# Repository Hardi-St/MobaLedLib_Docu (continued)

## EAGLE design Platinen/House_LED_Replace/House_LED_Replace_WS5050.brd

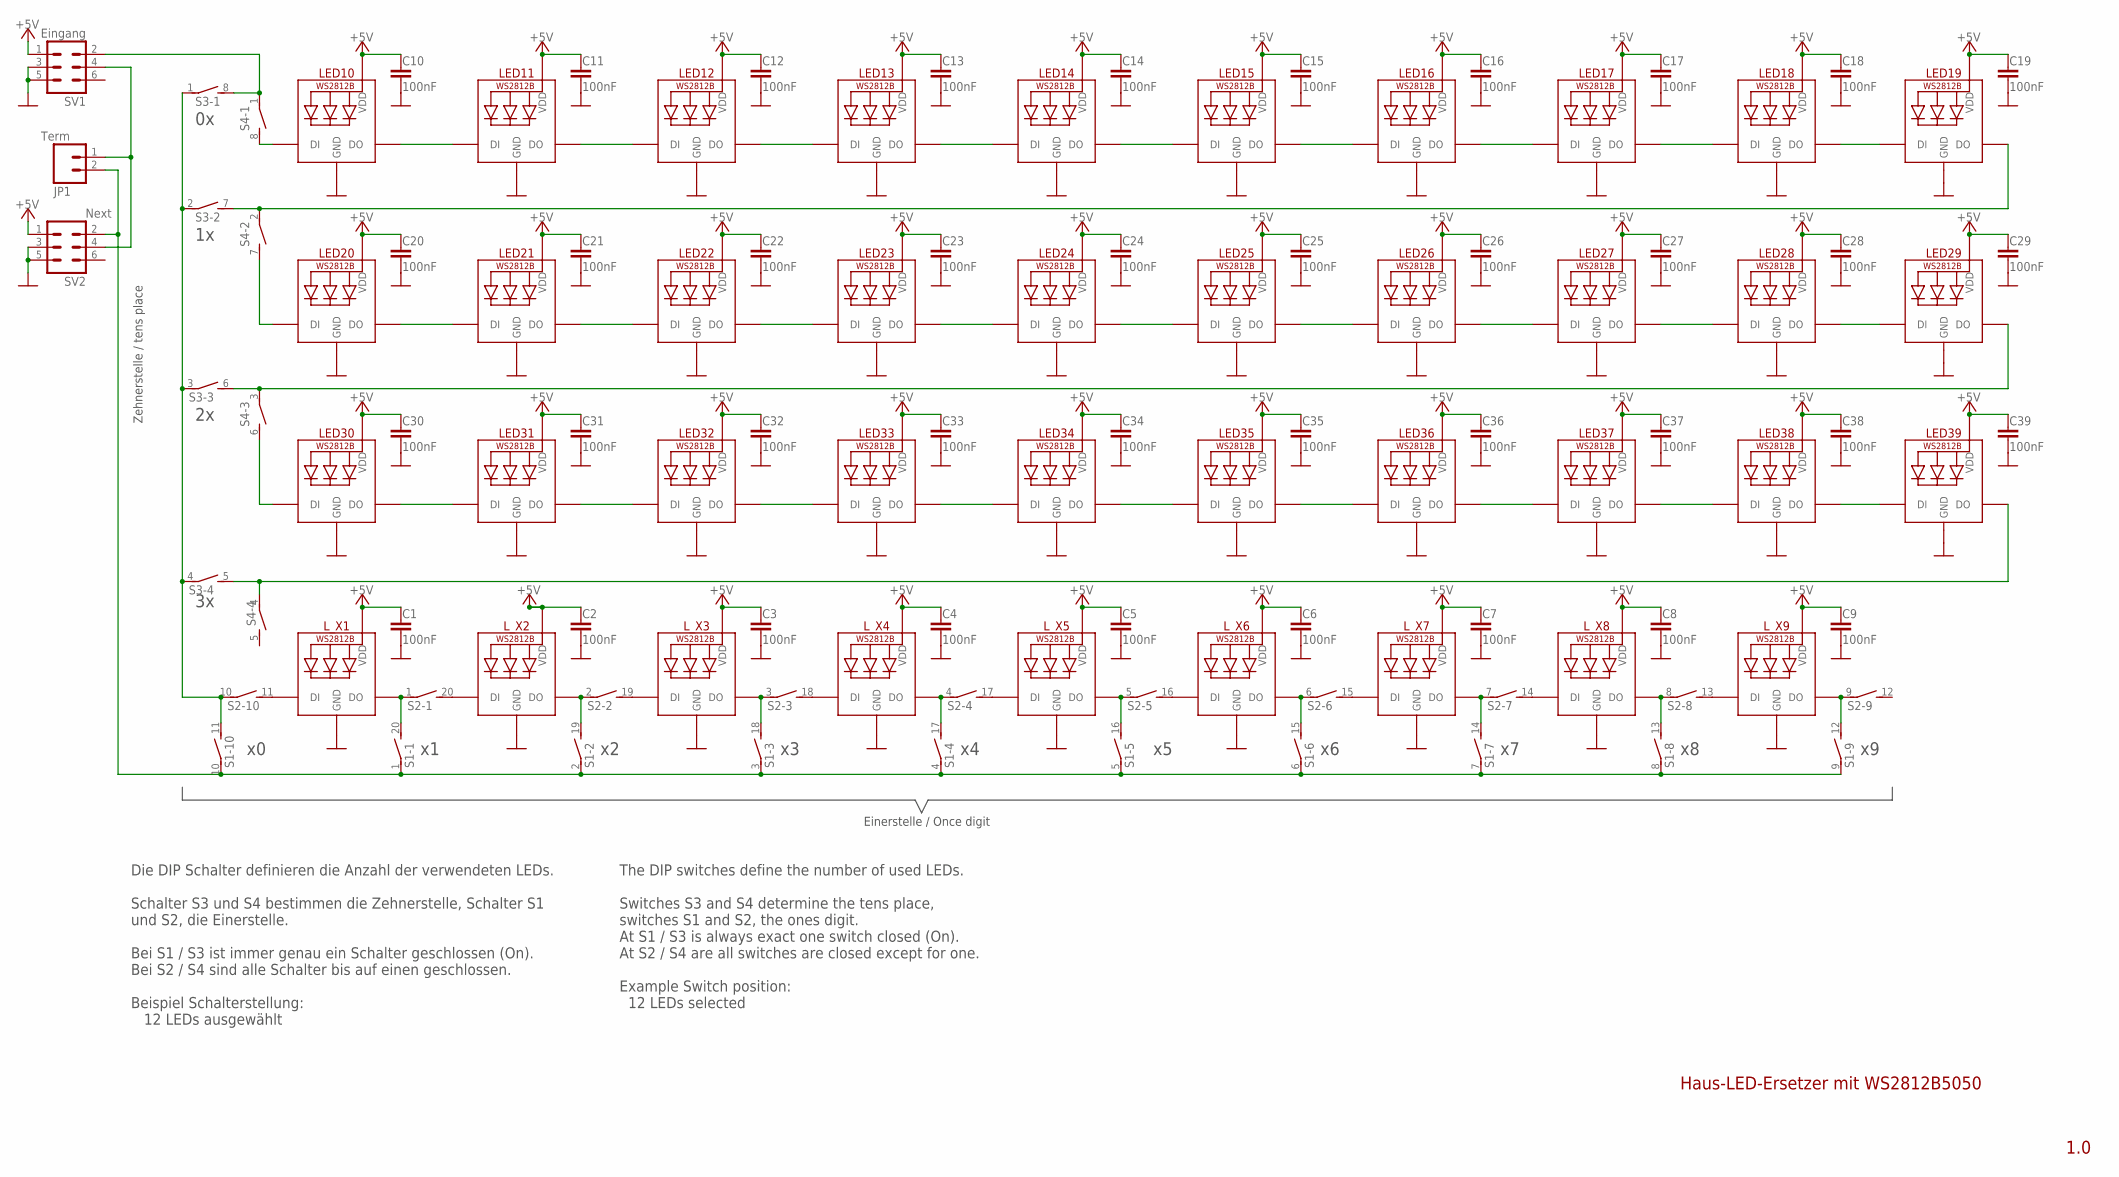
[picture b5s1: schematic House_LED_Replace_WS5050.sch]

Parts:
C1, C2, C3, C4, C5, C6, C7, C8, C9, C10, C11, C12, C13, C14, C15, C16, C17, C18, C19, C20, C21, C22, C23, C24, C25, C26, C27, C28, C29, C30, C31, C32, C33, C34, C35, C36, C37, C38, C39: 100nF; C0603
JP1: Term; 1X02
LED10, LED11, LED12, LED13, LED14, LED15, LED16, LED17, LED18, LED19, LED20, LED21, LED22, LED23, LED24, LED25, LED26, LED27, LED28, LED29, LED30, LED31, LED32, LED33, LED34, LED35, LED36, LED37, LED38, LED39: WS2812B5050; WS2812B
L_X1, L_X2, L_X3, L_X4, L_X5, L_X6, L_X7, L_X8, L_X9: WS2812B5050; WS2812B
S1, S2: DIP10SB
S3, S4: DIP04S
SV1: Eingang; ML6
SV2: Next; ML6

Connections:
+5V: C1.1, C2.1, C3.1, C4.1, C5.1, C6.1, C7.1, C8.1, C9.1, C10.1, C11.1, C12.1, C13.1, C14.1, C15.1, C16.1, C17.1, C18.1, C19.1, C20.1, C21.1, C22.1, C23.1, C24.1, C25.1, C26.1, C27.1, C28.1, C29.1, C30.1, C31.1, C32.1, C33.1, C34.1, C35.1, C36.1, C37.1, C38.1, C39.1, LED10.1-5V (VDD), LED11.1-5V (VDD), LED12.1-5V (VDD), LED13.1-5V (VDD), LED14.1-5V (VDD), LED15.1-5V (VDD), LED16.1-5V (VDD), LED17.1-5V (VDD), LED18.1-5V (VDD), LED19.1-5V (VDD), LED20.1-5V (VDD), LED21.1-5V (VDD), LED22.1-5V (VDD), LED23.1-5V (VDD), LED24.1-5V (VDD), LED25.1-5V (VDD), LED26.1-5V (VDD), LED27.1-5V (VDD), LED28.1-5V (VDD), LED29.1-5V (VDD), LED30.1-5V (VDD), LED31.1-5V (VDD), LED32.1-5V (VDD), LED33.1-5V (VDD), LED34.1-5V (VDD), LED35.1-5V (VDD), LED36.1-5V (VDD), LED37.1-5V (VDD), LED38.1-5V (VDD), LED39.1-5V (VDD), L_X1.1-5V (VDD), L_X2.1-5V (VDD), L_X3.1-5V (VDD), L_X4.1-5V (VDD), L_X5.1-5V (VDD), L_X6.1-5V (VDD), L_X7.1-5V (VDD), L_X8.1-5V (VDD), L_X9.1-5V (VDD), SV1.1, SV2.1
GND: C1.2, C2.2, C3.2, C4.2, C5.2, C6.2, C7.2, C8.2, C9.2, C10.2, C11.2, C12.2, C13.2, C14.2, C15.2, C16.2, C17.2, C18.2, C19.2, C20.2, C21.2, C22.2, C23.2, C24.2, C25.2, C26.2, C27.2, C28.2, C29.2, C30.2, C31.2, C32.2, C33.2, C34.2, C35.2, C36.2, C37.2, C38.2, C39.2, LED10.3-GND (GND), LED11.3-GND (GND), LED12.3-GND (GND), LED13.3-GND (GND), LED14.3-GND (GND), LED15.3-GND (GND), LED16.3-GND (GND), LED17.3-GND (GND), LED18.3-GND (GND), LED19.3-GND (GND), LED20.3-GND (GND), LED21.3-GND (GND), LED22.3-GND (GND), LED23.3-GND (GND), LED24.3-GND (GND), LED25.3-GND (GND), LED26.3-GND (GND), LED27.3-GND (GND), LED28.3-GND (GND), LED29.3-GND (GND), LED30.3-GND (GND), LED31.3-GND (GND), LED32.3-GND (GND), LED33.3-GND (GND), LED34.3-GND (GND), LED35.3-GND (GND), LED36.3-GND (GND), LED37.3-GND (GND), LED38.3-GND (GND), LED39.3-GND (GND), L_X1.3-GND (GND), L_X2.3-GND (GND), L_X3.3-GND (GND), L_X4.3-GND (GND), L_X5.3-GND (GND), L_X6.3-GND (GND), L_X7.3-GND (GND), L_X8.3-GND (GND), L_X9.3-GND (GND), SV1.3, SV1.5, SV2.3, SV2.5
unnamed: JP1.2, S1.1, S1.2 (1), S1.3 (1), S1.4 (1), S1.5 (1), S1.6 (1), S1.7 (1), S1.8 (1), S1.9 (1), S1.10 (1), SV2.2
unnamed: L_X1.2-DOUT (DO), S1.20 (2), S2.1
unnamed: L_X2.4-DIN (DI), S2.20 (2)
unnamed: L_X2.2-DOUT (DO), S1.19 (2), S2.2 (1)
unnamed: L_X3.4-DIN (DI), S2.19 (2)
unnamed: L_X3.2-DOUT (DO), S1.18 (2), S2.3 (1)
unnamed: L_X4.4-DIN (DI), S2.18 (2)
unnamed: L_X4.2-DOUT (DO), S1.17 (2), S2.4 (1)
unnamed: LED10.2-DOUT (DO), LED11.4-DIN (DI)
unnamed: LED11.2-DOUT (DO), LED12.4-DIN (DI)
unnamed: LED12.2-DOUT (DO), LED13.4-DIN (DI)
unnamed: LED13.2-DOUT (DO), LED14.4-DIN (DI)
unnamed: LED14.2-DOUT (DO), LED15.4-DIN (DI)
unnamed: LED15.2-DOUT (DO), LED16.4-DIN (DI)
unnamed: LED16.2-DOUT (DO), LED17.4-DIN (DI)
unnamed: LED17.2-DOUT (DO), LED18.4-DIN (DI)
unnamed: LED18.2-DOUT (DO), LED19.4-DIN (DI)
unnamed: LED30.2-DOUT (DO), LED31.4-DIN (DI)
unnamed: LED20.2-DOUT (DO), LED21.4-DIN (DI)
unnamed: LED21.2-DOUT (DO), LED22.4-DIN (DI)
unnamed: LED22.2-DOUT (DO), LED23.4-DIN (DI)
unnamed: LED23.2-DOUT (DO), LED24.4-DIN (DI)
unnamed: LED24.2-DOUT (DO), LED25.4-DIN (DI)
unnamed: LED25.2-DOUT (DO), LED26.4-DIN (DI)
unnamed: LED26.2-DOUT (DO), LED27.4-DIN (DI)
unnamed: LED27.2-DOUT (DO), LED28.4-DIN (DI)
unnamed: LED28.2-DOUT (DO), LED29.4-DIN (DI)
unnamed: LED31.2-DOUT (DO), LED32.4-DIN (DI)
unnamed: LED32.2-DOUT (DO), LED33.4-DIN (DI)
unnamed: LED33.2-DOUT (DO), LED34.4-DIN (DI)
unnamed: LED34.2-DOUT (DO), LED35.4-DIN (DI)
unnamed: LED35.2-DOUT (DO), LED36.4-DIN (DI)
unnamed: LED36.2-DOUT (DO), LED37.4-DIN (DI)
unnamed: LED37.2-DOUT (DO), LED38.4-DIN (DI)
unnamed: LED38.2-DOUT (DO), LED39.4-DIN (DI)
unnamed: L_X5.4-DIN (DI), S2.17 (2)
unnamed: L_X5.2-DOUT (DO), S1.16 (2), S2.5 (1)
unnamed: LED19.2-DOUT (DO), S3.7 (2), S4.2 (1)
unnamed: LED20.4-DIN (DI), S4.7 (2)
unnamed: L_X6.4-DIN (DI), S2.16 (2)
unnamed: LED30.4-DIN (DI), S4.6 (2)
unnamed: LED39.2-DOUT (DO), S3.5 (2), S4.4 (1)
unnamed: L_X6.2-DOUT (DO), S1.15 (2), S2.6 (1)
unnamed: L_X7.4-DIN (DI), S2.15 (2)
unnamed: L_X7.2-DOUT (DO), S1.14 (2), S2.7 (1)
unnamed: L_X8.4-DIN (DI), S2.14 (2)
unnamed: L_X8.2-DOUT (DO), S1.13 (2), S2.8 (1)
unnamed: LED10.4-DIN (DI), S4.8 (2)
unnamed: S3.8 (2), S4.1, SV1.2
unnamed: S1.11 (2), S2.10 (1), S3.1, S3.2 (1), S3.3 (1), S3.4 (1)
unnamed: L_X9.4-DIN (DI), S2.13 (2)
unnamed: L_X9.2-DOUT (DO), S1.12 (2), S2.9 (1)
unnamed: L_X1.4-DIN (DI), S2.11 (2)
unnamed: JP1.1, SV1.4, SV2.4
unnamed: LED29.2-DOUT (DO), S3.6 (2), S4.3 (1)

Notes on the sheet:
Die DIP Schalter definieren die Anzahl der verwendeten LEDs. Schalter S3 und S4 bestimmen die Zehnerstelle, Schalter S1 und S2, die Einerstelle. Bei S1 / S3 ist immer genau ein Schalter geschlossen (On). Bei S2 / S4 sind alle Schalter bis auf einen geschlossen. Beispiel Schalterstellung: 12 LEDs au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
Zehnerstelle / tens place
Einerstelle / Once digit
1.0
Haus-LED-Ersetzer mit WS2812B5050
The DIP switches define the number of used LEDs. Switches S3 and S4 determine the tens place, switches S1 and S2, the ones digit. At S1 / S3 is always exact one switch closed (On). At S2 / S4 are all switches are closed except for one. Example Switch position: 12 LEDs selected

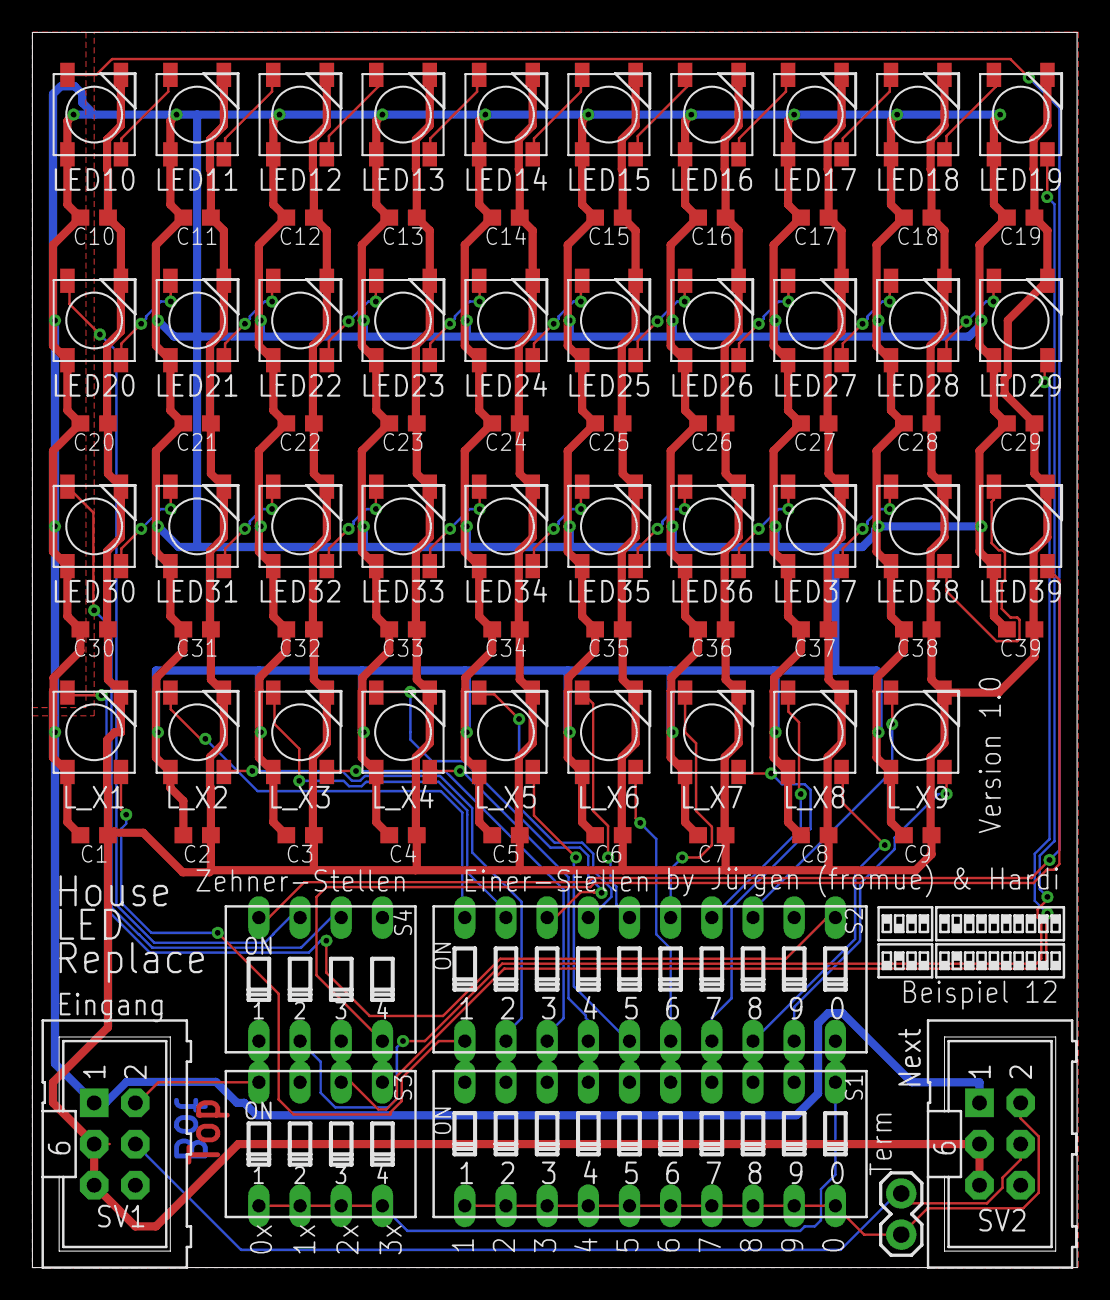
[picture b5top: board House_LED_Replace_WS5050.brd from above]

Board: 2 copper layers, 64.4 x 76.2 mm, 85 parts (0 on the bottom side), 57 nets.

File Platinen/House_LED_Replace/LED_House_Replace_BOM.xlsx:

Comment | Designator | Footprint | JLCPCB Part #（optional）
100nF | C1, C2, C3, C4, C5, C6, C7, C8, C9, C10, C11, C12, C13, C14, C15, C16, C17, C18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 | C0603 | C14663
WS2812B5050 | L_X1, L_X2, L_X3, L_X4, L_X5, L_X6, L_X7, L_X8, L_X9, LED10, LED11, LED12, LED1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 | WS2812B5050 | C2761795

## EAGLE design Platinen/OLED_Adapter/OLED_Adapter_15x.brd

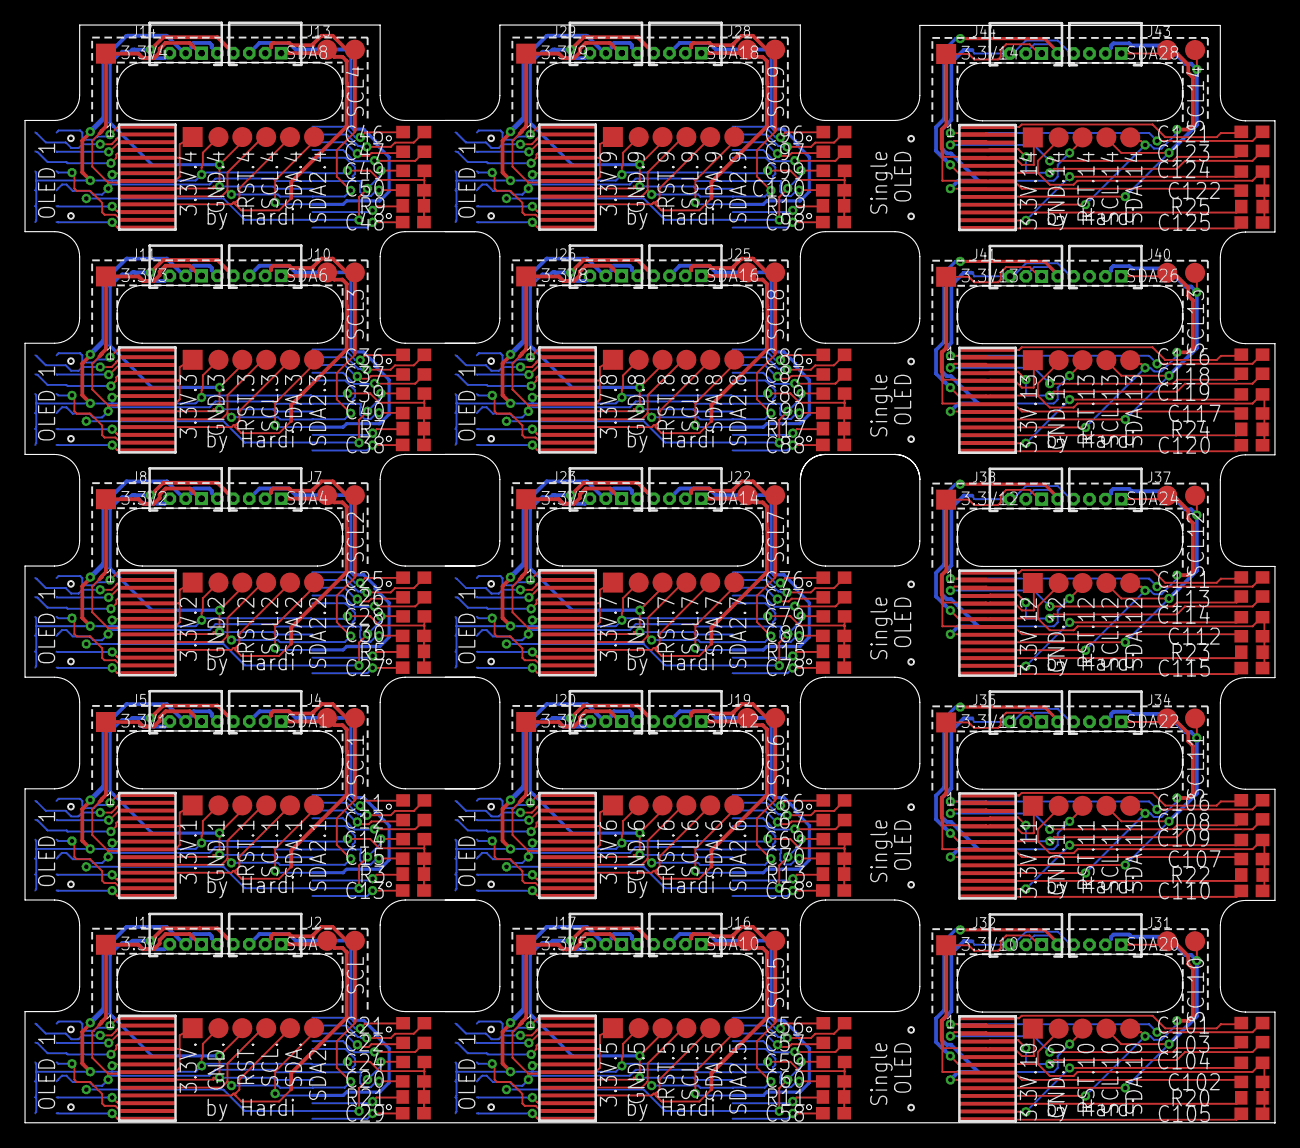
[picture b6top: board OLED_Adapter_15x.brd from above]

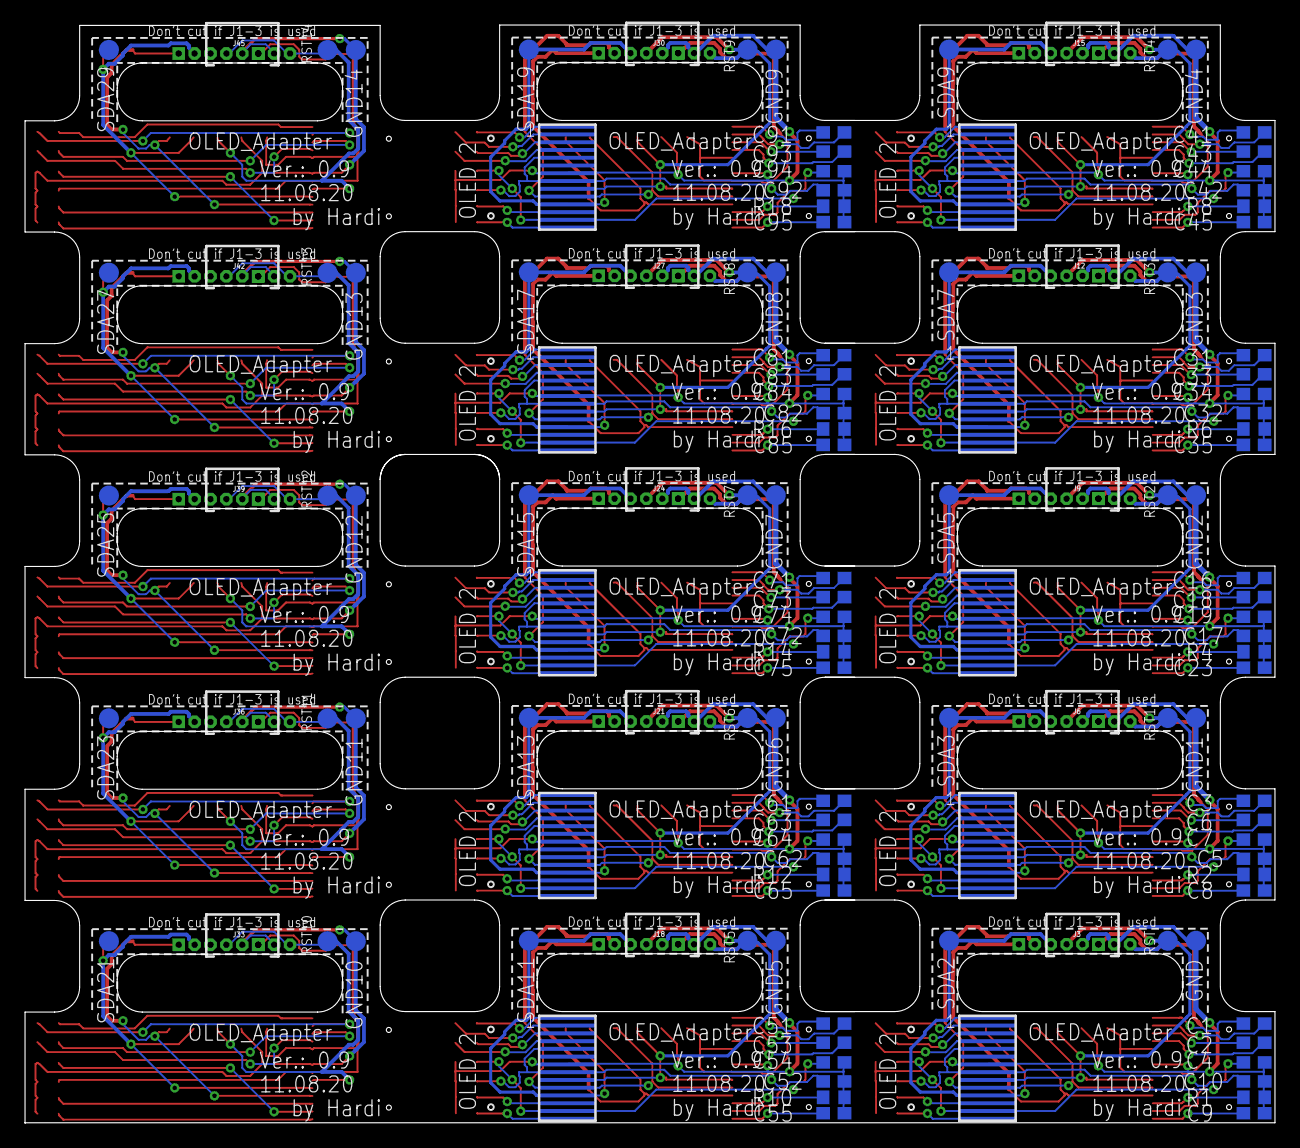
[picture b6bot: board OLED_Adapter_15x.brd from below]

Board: 2 copper layers, 99.8 x 87.7 mm, 395 parts (130 on the bottom side), 260 nets.

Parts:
3.3V, 3.3V1, 3.3V2, 3.3V3, 3.3V4, 3.3V5, 3.3V6, 3.3V7, 3.3V8, 3.3V9, 3.3V10, 3.3V11, 3.3V12, 3.3V13, 3.3V14: 3.3V; TP16SQ
3.3V., 3.3V.1, 3.3V.2, 3.3V.3, 3.3V.4, 3.3V.5, 3.3V.6, 3.3V.7, 3.3V.8, 3.3V.9, 3.3V.10, 3.3V.11, 3.3V.12, 3.3V.13, 3.3V.14: TPTP16SQ; TP16SQ
C1, C2, C3, C6, C11, C12, C16, C18, C21, C22, C25, C26, C31, C33, C36, C37, C41, C43, C46, C47, C51, C53, C56, C57, C61, C63, C66, C67, C71, C73, C76, C77, C81, C83, C86, C87, C91, C93, C96, C97, C101, C103, C106, C108, C111, C113, C116, C118, C121, C123: 470nF; C0603
C4, C7, C14, C19, C24, C28, C34, C39, C44, C49, C54, C59, C64, C69, C74, C79, C84, C89, C94, C99, C104, C109, C114, C119, C124: 2.2uF; C0603
C5, C8, C9, C10, C13, C15, C17, C20, C23, C27, C29, C30, C32, C35, C38, C40, C42, C45, C48, C50, C52, C55, C58, C60, C62, C65, C68, C70, C72, C75, C78, C80, C82, C85, C88, C90, C92, C95, C98, C100, C102, C105, C107, C110, C112, C115, C117, C120, C122, C125: 4.7uF; C0603
GND, GND1, GND2, GND3, GND4, GND5, GND6, GND7, GND8, GND9, GND10, GND11, GND12, GND13, GND14: GND; TP16R
GND., GND.1, GND.2, GND.3, GND.4, GND.5, GND.6, GND.7, GND.8, GND.9, GND.10, GND.11, GND.12, GND.13, GND.14: TPTP16R; TP16R
IC1, IC2, IC3, IC4, IC5, IC6, IC7, IC8, IC9, IC10, IC11, IC12, IC13, IC14, IC15, IC16, IC17, IC18, IC19, IC20, IC21, IC22, IC23, IC24, IC25: OLED_FLEXW_DISP; OLED_FLEX_W_DISP
J1, J2, J3, J4, J5, J6, J7, J8, J9, J10, J11, J12, J13, J14, J15, J16, J17, J18, J19, J20, J21, J22, J23, J24, J25, J26, J27, J28, J29, J30, J31, J32, J33, J34, J35, J36, J37, J38, J39, J40, J41, J42, J43, J44, J45: SV3; MINI
R1, R2, R3, R4, R5, R6, R7, R8, R9, R10, R11, R12, R13, R14, R15, R16, R17, R18, R19, R20, R21, R22, R23, R24, R25: 560K; R0603
RST, RST1, RST2, RST3, RST4, RST5, RST6, RST7, RST8, RST9, RST10, RST11, RST12, RST13, RST14: RST; TP16R
RST., RST.1, RST.2, RST.3, RST.4, RST.5, RST.6, RST.7, RST.8, RST.9, RST.10, RST.11, RST.12, RST.13, RST.14: TPTP16R; TP16R
SCL, SCL1, SCL2, SCL3, SCL4, SCL5, SCL6, SCL7, SCL8, SCL9, SCL10, SCL11, SCL12, SCL13, SCL14: SCL; TP16R
SCL., SCL.1, SCL.2, SCL.3, SCL.4, SCL.5, SCL.6, SCL.7, SCL.8, SCL.9, SCL.10, SCL.11, SCL.12, SCL.13, SCL.14: TPTP16R; TP16R
SDA, SDA1, SDA4, SDA6, SDA8, SDA10, SDA12, SDA14, SDA16, SDA18, SDA20, SDA22, SDA24, SDA26, SDA28: SDA; TP16R
SDA2, SDA3, SDA5, SDA7, SDA9, SDA11, SDA13, SDA15, SDA17, SDA19, SDA21, SDA23, SDA25, SDA27, SDA29: SDA2; TP16R
SDA2., SDA2.1, SDA2.2, SDA2.3, SDA2.4, SDA2.5, SDA2.6, SDA2.7, SDA2.8, SDA2.9, SDA., SDA.1, SDA.2, SDA.3, SDA.4, SDA.5, SDA.6, SDA.7, SDA.8, SDA.9, SDA.10, SDA.11, SDA.12, SDA.13, SDA.14: TPTP16R; TP16R

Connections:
3.3V: 3.3V.TP, 3.3V..TP, C10.1, C20.1, IC1.5, IC1.8, IC2.5, IC2.8, J1.1, J3.1
3.3V1: 3.3V1.TP, 3.3V.1.TP, C5.1, C15.1, IC3.5, IC3.8, IC4.5, IC4.8, J5.1, J6.1
3.3V2: 3.3V2.TP, 3.3V.2.TP, C17.1, C30.1, IC5.5, IC5.8, IC6.5, IC6.8, J8.1, J9.1
3.3V3: 3.3V3.TP, 3.3V.3.TP, C32.1, C40.1, IC7.5, IC7.8, IC8.5, IC8.8, J11.1, J12.1
3.3V4: 3.3V4.TP, 3.3V.4.TP, C42.1, C50.1, IC9.5, IC9.8, IC10.5, IC10.8, J14.1, J15.1
3.3V5: 3.3V5.TP, 3.3V.5.TP, C52.1, C60.1, IC11.5, IC11.8, IC12.5, IC12.8, J17.1, J18.1
3.3V6: 3.3V6.TP, 3.3V.6.TP, C62.1, C70.1, IC13.5, IC13.8, IC14.5, IC14.8, J20.1, J21.1
3.3V7: 3.3V7.TP, 3.3V.7.TP, C72.1, C80.1, IC15.5, IC15.8, IC16.5, IC16.8, J23.1, J24.1
3.3V8: 3.3V8.TP, 3.3V.8.TP, C82.1, C90.1, IC17.5, IC17.8, IC18.5, IC18.8, J26.1, J27.1
3.3V9: 3.3V9.TP, 3.3V.9.TP, C92.1, C100.1, IC19.5, IC19.8, IC20.5, IC20.8, J29.1, J30.1
3.3V10: 3.3V10.TP, 3.3V.10.TP, C102.1, IC21.5, IC21.8, J32.1, J33.1
3.3V11: 3.3V11.TP, 3.3V.11.TP, C107.1, IC22.5, IC22.8, J35.1, J36.1
3.3V12: 3.3V12.TP, 3.3V.12.TP, C112.1, IC23.5, IC23.8, J38.1, J39.1
3.3V13: 3.3V13.TP, 3.3V.13.TP, C117.1, IC24.5, IC24.8, J41.1, J42.1
3.3V14: 3.3V14.TP, 3.3V.14.TP, C122.1, IC25.5, IC25.8, J44.1, J45.1
GND: C4.1, C9.2, C10.2, C20.2, C24.1, C29.2, GND.TP, GND..TP, IC1.7, IC2.7, J1.2, J3.2, R1.1, R21.1
GND1: C5.2, C7.1, C8.2, C13.2, C14.1, C15.2, GND1.TP, GND.1.TP, IC3.7, IC4.7, J5.2, J6.2, R2.1, R3.1
GND2: C17.2, C19.1, C23.2, C27.2, C28.1, C30.2, GND2.TP, GND.2.TP, IC5.7, IC6.7, J8.2, J9.2, R4.1, R5.1
GND3: C32.2, C34.1, C35.2, C38.2, C39.1, C40.2, GND3.TP, GND.3.TP, IC7.7, IC8.7, J11.2, J12.2, R6.1, R7.1
GND4: C42.2, C44.1, C45.2, C48.2, C49.1, C50.2, GND4.TP, GND.4.TP, IC9.7, IC10.7, J14.2, J15.2, R8.1, R9.1
GND5: C52.2, C54.1, C55.2, C58.2, C59.1, C60.2, GND5.TP, GND.5.TP, IC11.7, IC12.7, J17.2, J18.2, R10.1, R11.1
GND6: C62.2, C64.1, C65.2, C68.2, C69.1, C70.2, GND6.TP, GND.6.TP, IC13.7, IC14.7, J20.2, J21.2, R12.1, R13.1
GND7: C72.2, C74.1, C75.2, C78.2, C79.1, C80.2, GND7.TP, GND.7.TP, IC15.7, IC16.7, J23.2, J24.2, R14.1, R15.1
GND8: C82.2, C84.1, C85.2, C88.2, C89.1, C90.2, GND8.TP, GND.8.TP, IC17.7, IC18.7, J26.2, J27.2, R16.1, R17.1
GND9: C92.2, C94.1, C95.2, C98.2, C99.1, C100.2, GND9.TP, GND.9.TP, IC19.7, IC20.7, J29.2, J30.2, R18.1, R19.1
GND10: C102.2, C104.1, C105.2, GND10.TP, GND.10.TP, IC21.7, J32.2, J33.2, R20.1
GND11: C107.2, C109.1, C110.2, GND11.TP, GND.11.TP, IC22.7, J35.2, J36.2, R22.1
GND12: C112.2, C114.1, C115.2, GND12.TP, GND.12.TP, IC23.7, J38.2, J39.2, R23.1
GND13: C117.2, C119.1, C120.2, GND13.TP, GND.13.TP, IC24.7, J41.2, J42.2, R24.1
GND14: C122.2, C124.1, C125.2, GND14.TP, GND.14.TP, IC25.7, J44.2, J45.2, R25.1
unnamed: IC1.12, R1.2
unnamed: C21.2, IC2.1
unnamed: C1.2, IC1.1
unnamed: C1.1, IC1.2
unnamed: C2.2, IC1.3
unnamed: C2.1, IC1.4
unnamed: C9.1, IC1.14
unnamed: C4.2, IC1.13
unnamed: C21.1, IC2.2
unnamed: C22.2, IC2.3
unnamed: C22.1, IC2.4
unnamed: IC2.12, R21.2
unnamed: C29.1, IC2.14
unnamed: C24.2, IC2.13
unnamed: C3.2, IC3.1
unnamed: C3.1, IC3.2
unnamed: C6.2, IC3.3
unnamed: C6.1, IC3.4
unnamed: IC3.12, R2.2
unnamed: C8.1, IC3.14
unnamed: C7.2, IC3.13
unnamed: C11.2, IC4.1
unnamed: C11.1, IC4.2
unnamed: C12.2, IC4.3
unnamed: C12.1, IC4.4
unnamed: IC4.12, R3.2
unnamed: C13.1, IC4.14
unnamed: C14.2, IC4.13
unnamed: C16.2, IC5.1
unnamed: C16.1, IC5.2
unnamed: C18.2, IC5.3
unnamed: C18.1, IC5.4
unnamed: IC5.12, R4.2
unnamed: C23.1, IC5.14
unnamed: C19.2, IC5.13
unnamed: C25.2, IC6.1
unnamed: C25.1, IC6.2
unnamed: C26.2, IC6.3
unnamed: C26.1, IC6.4
unnamed: IC6.12, R5.2
unnamed: C27.1, IC6.14
unnamed: C28.2, IC6.13
unnamed: C31.2, IC7.1
unnamed: C31.1, IC7.2
unnamed: C33.2, IC7.3
unnamed: C33.1, IC7.4
unnamed: IC7.12, R6.2
unnamed: C35.1, IC7.14
unnamed: C34.2, IC7.13
unnamed: C36.2, IC8.1
unnamed: C36.1, IC8.2
unnamed: C37.2, IC8.3
unnamed: C37.1, IC8.4
unnamed: IC8.12, R7.2
unnamed: C38.1, IC8.14
unnamed: C39.2, IC8.13
unnamed: C41.2, IC9.1
unnamed: C41.1, IC9.2
unnamed: C43.2, IC9.3
unnamed: C43.1, IC9.4
unnamed: IC9.12, R8.2
unnamed: C45.1, IC9.14
unnamed: C44.2, IC9.13
unnamed: C46.2, IC10.1
unnamed: C46.1, IC10.2
unnamed: C47.2, IC10.3
unnamed: C47.1, IC10.4
unnamed: IC10.12, R9.2
unnamed: C48.1, IC10.14
unnamed: C49.2, IC10.13
unnamed: C51.2, IC11.1
unnamed: C51.1, IC11.2
unnamed: C53.2, IC11.3
unnamed: C53.1, IC11.4
unnamed: IC11.12, R10.2
unnamed: C55.1, IC11.14
unnamed: C54.2, IC11.13
unnamed: C56.2, IC12.1
unnamed: C56.1, IC12.2
unnamed: C57.2, IC12.3
unnamed: C57.1, IC12.4
unnamed: IC12.12, R11.2
unnamed: C58.1, IC12.14
unnamed: C59.2, IC12.13
unnamed: C61.2, IC13.1
unnamed: C61.1, IC13.2
unnamed: C63.2, IC13.3
unnamed: C63.1, IC13.4
unnamed: IC13.12, R12.2
unnamed: C65.1, IC13.14
unnamed: C64.2, IC13.13
unnamed: C66.2, IC14.1
unnamed: C66.1, IC14.2
unnamed: C67.2, IC14.3
unnamed: C67.1, IC14.4
unnamed: IC14.12, R13.2
unnamed: C68.1, IC14.14
unnamed: C69.2, IC14.13
unnamed: C71.2, IC15.1
unnamed: C71.1, IC15.2
unnamed: C73.2, IC15.3
unnamed: C73.1, IC15.4
unnamed: IC15.12, R14.2
unnamed: C75.1, IC15.14
unnamed: C74.2, IC15.13
unnamed: C76.2, IC16.1
unnamed: C76.1, IC16.2
unnamed: C77.2, IC16.3
unnamed: C77.1, IC16.4
unnamed: IC16.12, R15.2
unnamed: C78.1, IC16.14
unnamed: C79.2, IC16.13
unnamed: C81.2, IC17.1
unnamed: C81.1, IC17.2
unnamed: C83.2, IC17.3
unnamed: C83.1, IC17.4
unnamed: IC17.12, R16.2
unnamed: C85.1, IC17.14
unnamed: C84.2, IC17.13
unnamed: C86.2, IC18.1
unnamed: C86.1, IC18.2
unnamed: C87.2, IC18.3
unnamed: C87.1, IC18.4
unnamed: IC18.12, R17.2
unnamed: C88.1, IC18.14
unnamed: C89.2, IC18.13
unnamed: C91.2, IC19.1
unnamed: C91.1, IC19.2
unnamed: C93.2, IC19.3
unnamed: C93.1, IC19.4
unnamed: IC19.12, R18.2
unnamed: C95.1, IC19.14
unnamed: C94.2, IC19.13
unnamed: C96.2, IC20.1
unnamed: C96.1, IC20.2
unnamed: C97.2, IC20.3
unnamed: C97.1, IC20.4
unnamed: IC20.12, R19.2
unnamed: C98.1, IC20.14
unnamed: C99.2, IC20.13
unnamed: C101.2, IC21.1
unnamed: C101.1, IC21.2
unnamed: C103.2, IC21.3
unnamed: C103.1, IC21.4
unnamed: IC21.12, R20.2
unnamed: C105.1, IC21.14
unnamed: C104.2, IC21.13
unnamed: C106.2, IC22.1
unnamed: C106.1, IC22.2
unnamed: C108.2, IC22.3
unnamed: C108.1, IC22.4
unnamed: IC22.12, R22.2
unnamed: C110.1, IC22.14
unnamed: C109.2, IC22.13
unnamed: C111.2, IC23.1
unnamed: C111.1, IC23.2
unnamed: C113.2, IC23.3
unnamed: C113.1, IC23.4
unnamed: IC23.12, R23.2
unnamed: C115.1, IC23.14
unnamed: C114.2, IC23.13
unnamed: C116.2, IC24.1
unnamed: C116.1, IC24.2
unnamed: C118.2, IC24.3
unnamed: C118.1, IC24.4
unnamed: IC24.12, R24.2
unnamed: C120.1, IC24.14
unnamed: C119.2, IC24.13
unnamed: C121.2, IC25.1
unnamed: C121.1, IC25.2
unnamed: C123.2, IC25.3
unnamed: C123.1, IC25.4
unnamed: IC25.12, R25.2
unnamed: C125.1, IC25.14
unnamed: C124.2, IC25.13
RES#: IC1.9, IC2.9, J1.3, J3.3, RST.TP, RST..TP
RES#1: IC3.9, IC4.9, J5.3, J6.3, RST1.TP, RST.1.TP
RES#2: IC5.9, IC6.9, J8.3, J9.3, RST2.TP, RST.2.TP
RES#3: IC7.9, IC8.9, J11.3, J12.3, RST3.TP, RST.3.TP
RES#4: IC9.9, IC10.9, J14.3, J15.3, RST4.TP, RST.4.TP
RES#5: IC11.9, IC12.9, J17.3, J18.3, RST5.TP, RST.5.TP
RES#6: IC13.9, IC14.9, J20.3, J21.3, RST6.TP, RST.6.TP
RES#7: IC15.9, IC16.9, J23.3, J24.3, RST7.TP, RST.7.TP
RES#8: IC17.9, IC18.9, J26.3, J27.3, RST8.TP, RST.8.TP
RES#9: IC19.9, IC20.9, J29.3, J30.3, RST9.TP, RST.9.TP
RES#10: IC21.9, J32.3, J33.3, RST10.TP, RST.10.TP
RES#11: IC22.9, J35.3, J36.3, RST11.TP, RST.11.TP
RES#12: IC23.9, J38.3, J39.3, RST12.TP, RST.12.TP
RES#13: IC24.9, J41.3, J42.3, RST13.TP, RST.13.TP
RES#14: IC25.9, J44.3, J45.3, RST14.TP, RST.14.TP
SCL: IC1.10, IC2.10, J2.2, SCL.TP, SCL..TP
SCL1: IC3.10, IC4.10, J4.2, SCL1.TP, SCL.1.TP
SCL2: IC5.10, IC6.10, J7.2, SCL2.TP, SCL.2.TP
SCL3: IC7.10, IC8.10, J10.2, SCL3.TP, SCL.3.TP
SCL4: IC9.10, IC10.10, J13.2, SCL4.TP, SCL.4.TP
SCL5: IC11.10, IC12.10, J16.2, SCL5.TP, SCL.5.TP
SCL6: IC13.10, IC14.10, J19.2, SCL6.TP, SCL.6.TP
SCL7: IC15.10, IC16.10, J22.2, SCL7.TP, SCL.7.TP
SCL8: IC17.10, IC18.10, J25.2, SCL8.TP, SCL.8.TP
SCL9: IC19.10, IC20.10, J28.2, SCL9.TP, SCL.9.TP
SCL10: IC21.10, J31.2, SCL10.TP, SCL.10.TP
SCL11: IC22.10, J34.2, SCL11.TP, SCL.11.TP
SCL12: IC23.10, J37.2, SCL12.TP, SCL.12.TP
SCL13: IC24.10, J40.2, SCL13.TP, SCL.13.TP
SCL14: IC25.10, J43.2, SCL14.TP, SCL.14.TP
SDA: IC1.11, J2.1, SDA.TP, SDA..TP
SDA1: IC3.11, J4.1, SDA1.TP, SDA.1.TP
SDA2: IC2.11, J2.3, SDA2.TP, SDA2..TP
SDA3: IC4.11, J4.3, SDA2.1.TP, SDA3.TP
SDA4: IC5.11, J7.1, SDA4.TP, SDA.2.TP
SDA5: IC6.11, J7.3, SDA2.2.TP, SDA5.TP
SDA6: IC7.11, J10.1, SDA6.TP, SDA.3.TP
SDA7: IC8.11, J10.3, SDA2.3.TP, SDA7.TP
SDA8: IC9.11, J13.1, SDA8.TP, SDA.4.TP
SDA9: IC10.11, J13.3, SDA2.4.TP, SDA9.TP
SDA10: IC11.11, J16.1, SDA10.TP, SDA.5.TP
SDA11: IC12.11, J16.3, SDA2.5.TP, SDA11.TP
SDA12: IC13.11, J19.1, SDA12.TP, SDA.6.TP
SDA13: IC14.11, J19.3, SDA2.6.TP, SDA13.TP
SDA14: IC15.11, J22.1, SDA14.TP, SDA.7.TP
SDA15: IC16.11, J22.3, SDA2.7.TP, SDA15.TP
SDA16: IC17.11, J25.1, SDA16.TP, SDA.8.TP
SDA17: IC18.11, J25.3, SDA2.8.TP, SDA17.TP
SDA18: IC19.11, J28.1, SDA18.TP, SDA.9.TP
SDA19: IC20.11, J28.3, SDA2.9.TP, SDA19.TP
SDA20: IC21.11, J31.1, SDA20.TP, SDA.10.TP
SDA21: IC22.11, J34.1, SDA22.TP, SDA.11.TP
SDA22: IC23.11, J37.1, SDA24.TP, SDA.12.TP
SDA23: IC24.11, J40.1, SDA26.TP, SDA.13.TP
SDA24: IC25.11, J43.1, SDA28.TP, SDA.14.TP
